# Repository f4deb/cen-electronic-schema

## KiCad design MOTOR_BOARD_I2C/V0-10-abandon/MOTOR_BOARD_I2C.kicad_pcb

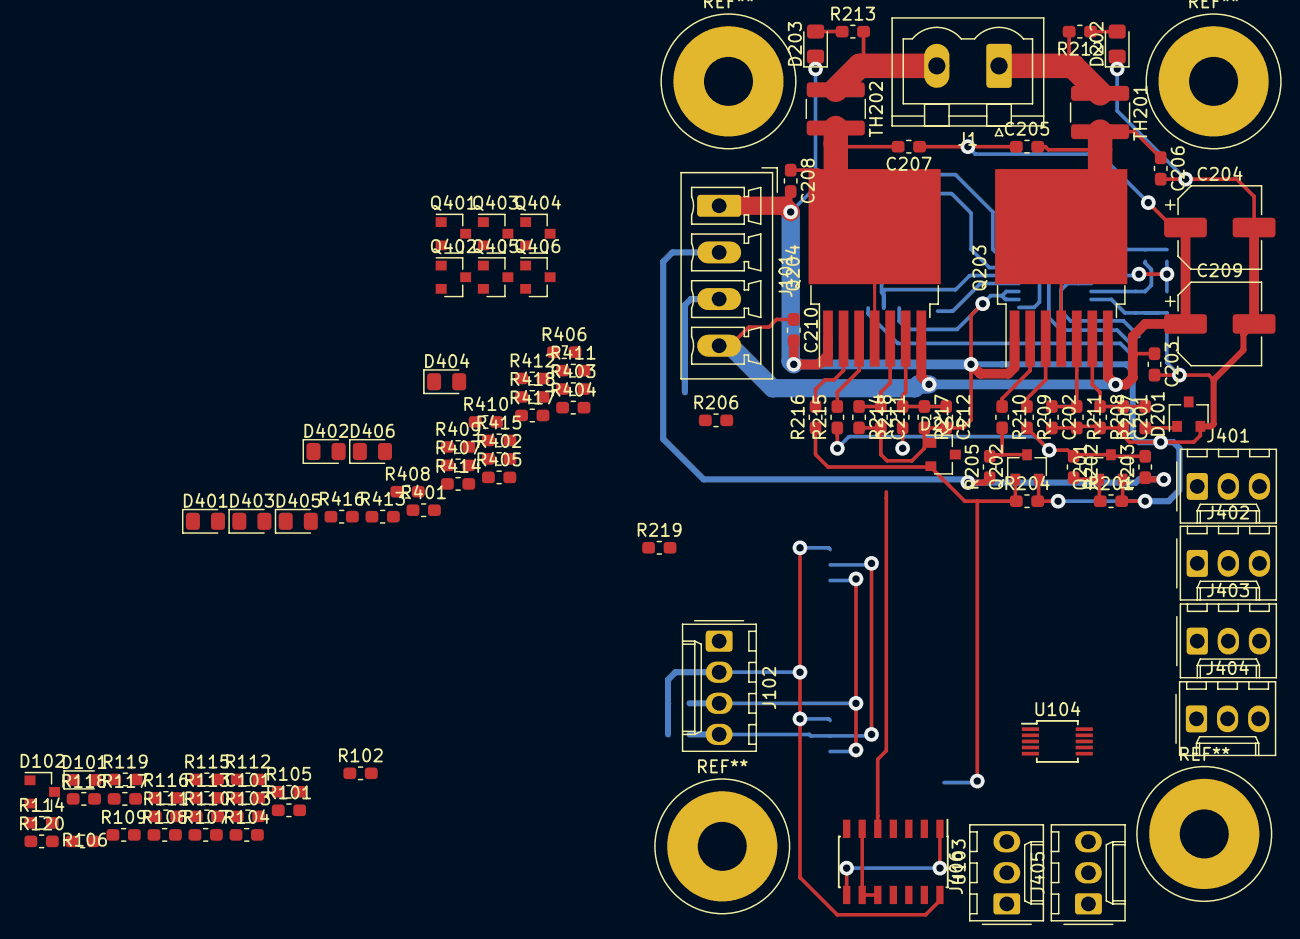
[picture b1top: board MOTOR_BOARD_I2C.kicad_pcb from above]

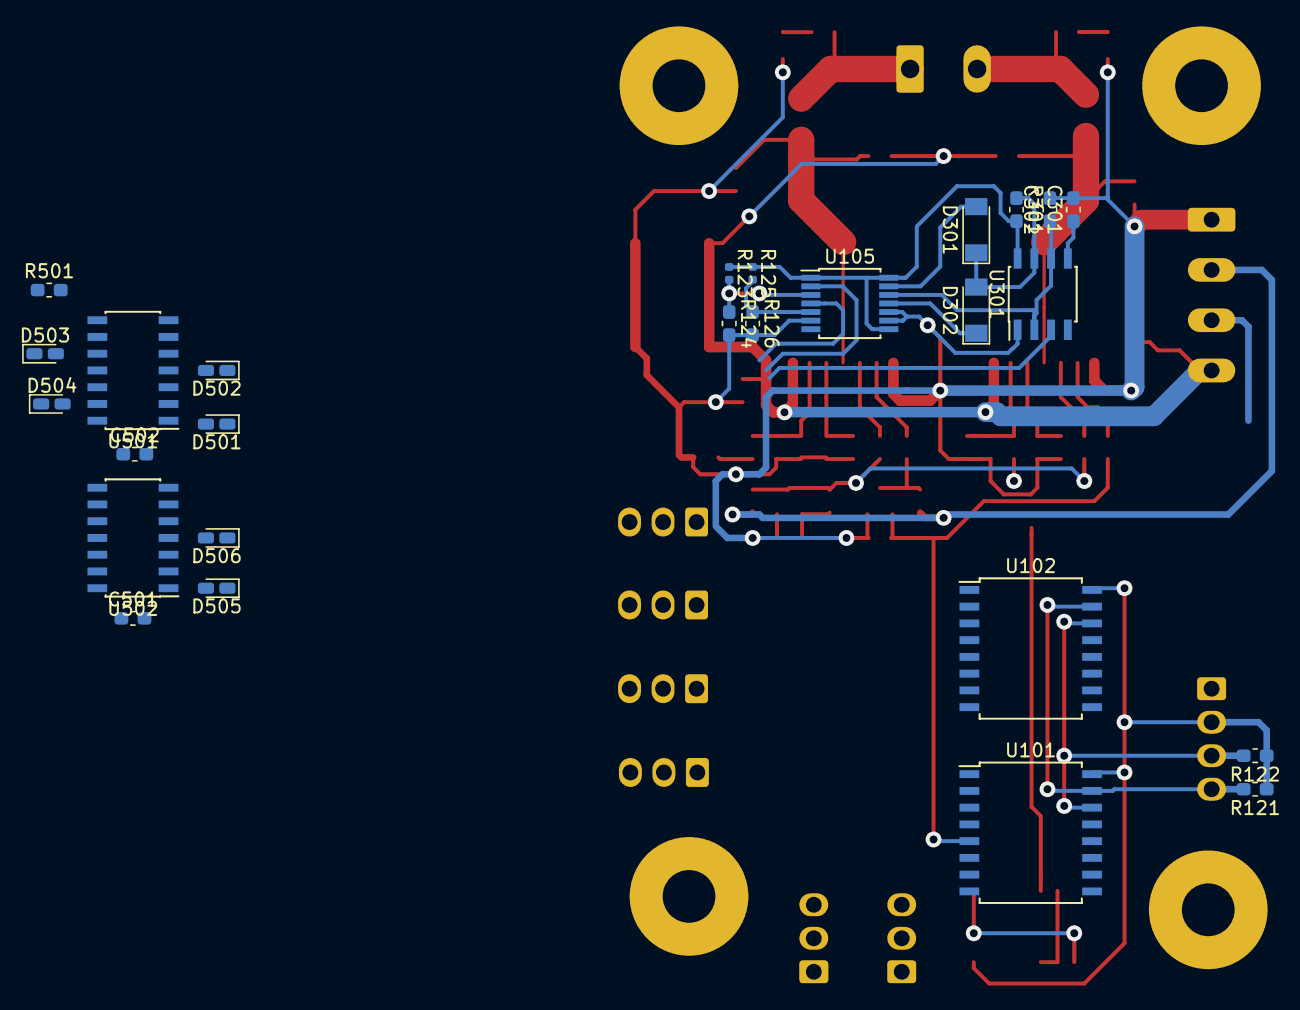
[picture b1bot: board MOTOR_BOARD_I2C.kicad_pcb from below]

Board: 2 copper layers, 131 parts (26 on the bottom side), 81 nets.

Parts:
C101, C203, C210, C501, C502: 100n; C_0603_1608Metric_Pad1.05x0.95mm_HandSolder
C201, C202, C211, C212, C302: C; C_0603_1608Metric_Pad1.05x0.95mm_HandSolder
C204, C209: 1000µ; CP_Elec_6.3x5.4
C205, C206, C207, C208: 220n; C_0603_1608Metric_Pad1.05x0.95mm_HandSolder
C301: 10n; C_0603_1608Metric_Pad1.05x0.95mm_HandSolder
D101: Jaune; LED_0603_1608Metric_Pad1.05x0.95mm_HandSolder
D102: D_Zener; SOT-23
D201, D204: D_Zener_Small_ALT; SOT-23
D202, D203, D401, D402, D403, D404, D405, D406: LED; LED_0805_2012Metric_Pad1.15x1.40mm_HandSolder
D301, D302: LL4148; D_MiniMELF
D501, D502, D503, D504, D505, D506: B140-E3; D_0603_1608Metric_Castellated
J1: Conn_01x02; PhoenixContact_MSTBVA_2,5_2-G-5,08_1x02_P5.08mm_Vertical
J101: Conn_01x04; PhoenixContact_MCV_1,5_4-G-3.81_1x04_P3.81mm_Vertical
J102: Conn_01x04; Molex_KK-254_AE-6410-04A_1x04_P2.54mm_Vertical
J401, J402, J403, J404, J405, J406: Conn_01x03_Male; Molex_KK-254_AE-6410-03A_1x03_P2.54mm_Vertical
Q201, Q202, Q401, Q402, Q403, Q404, Q405, Q406: 2N7002; SOT-23
Q203, Q204: BTN8982TA; TO-263-7_TabPin4
R101, R103, R105, R107, R109, R111, R115, R117, R119: 0; R_0603_1608Metric_Pad1.05x0.95mm_HandSolder
R102, R104, R106, R108, R110, R112, R116, R118, R120, R121, R122, R124, R126, R203, R205, R209, R210, R215, R216, R501: 10k; R_0603_1608Metric_Pad1.05x0.95mm_HandSolder
R113, R114, R405, R406, R411, R412, R417, R418: 1k; R_0603_1608Metric_Pad1.05x0.95mm_HandSolder
R123, R125: 0; R_0402_1005Metric
R201, R204, R403, R404, R409, R410, R415, R416: 100k; R_0603_1608Metric_Pad1.05x0.95mm_HandSolder
R202: NC-0; R_0603_1608Metric_Pad1.05x0.95mm_HandSolder
R206, R207, R208, R211, R212, R213, R214, R217, R218, R219, R301: R; R_0603_1608Metric_Pad1.05x0.95mm_HandSolder
R401, R402, R407, R408, R413, R414: 100; R_0603_1608Metric_Pad1.05x0.95mm_HandSolder
TH201, TH202: Thermistor; R_1218_3246Metric_Pad1.22x4.75mm_HandSolder
U101, U102: PCF8574A; SOIC-16W_7.5x10.3mm_P1.27mm
U103: 74HC00; SOIC-14_3.9x8.7mm_P1.27mm
U104: MCP3427-xUN; MSOP-10_3x3mm_P0.5mm
U105: MCP45HV31-ST; TSSOP-14_4.4x5mm_P0.65mm
U301: LM555; SOIC-8_3.9x4.9mm_P1.27mm
U501, U502: 74HC02; SOIC-14_3.9x8.7mm_P1.27mm

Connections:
+5VD: C501.1, C502.1, D401.2, D402.2, D403.2, D404.2, D405.2, D406.2, J101.2, J102.2, J401.2, J402.2, J403.2, J404.2, J405.2, J406.2, R101.1, R103.1, R105.1, R107.1, R109.1, R111.1, R114.1, R115.1, R117.1, R119.1, R121.1, R122.1, R123.1, R125.1, R203.1, R205.1, R301.2, U101.16, U102.16, U103.14, U105.1, U105.8, U105.14, U301.4, U301.8, U501.14, U502.14
+15V: C203.1, C204.1, C205.1, C207.1, C209.1, C210.1, J101.4, Q203.7, Q204.7
/IN0: Q401.3, R405.2, U102.6, U501.2
/IN1: Q403.3, R411.2, U102.7, U501.5
/IN2: Q405.3, R417.2, U102.9, U501.8
/IN3: Q402.3, R406.2, U102.10, U501.11
/IN4: Q404.3, R412.2, U102.11, U502.2
/IN5: Q406.3, R418.2, U102.12, U502.5
/IS1: R206.1, U102.4
/IS2: R219.1, U102.5
/M1A: J1.1, R212.2, TH201.1
/M1B: J1.2, R213.2, TH202.1
/PWM: U103.5, U301.3
/SCL: J102.3, R122.2, U101.14, U102.14, U105.2
/SDA: J102.4, R121.2, U101.15, U102.15, U105.4
/STOPMOTOR: U103.4, U502.13
/Sheet5DBEC701/S0: D501.2, U501.1
/Sheet5DBEC701/S1: D502.2, U501.4
/Sheet5DBEC701/S2: D503.2, U501.10
/Sheet5DBEC701/S3: D504.2, U501.13
/Sheet5DBEC701/S4: D505.2, U502.1
/Sheet5DBEC701/S5: D506.2, U502.4
/Sheet5DC0EE77/DIR1: Q202.1, R204.1, R216.1, U101.5
/Sheet5DC0EE77/PWM1: Q201.1, R201.1, R202.2, U103.3
/Sheet5DC7BBDF/Ra: D301.2, U105.13
/Sheet5DC7BBDF/Rb: D302.1, U105.11
/Sheet5DC7BBDF/Rw: C302.1, U105.12, U301.2, U301.6
GND: C101.2, C201.2, C202.2, C203.2, C204.2, C206.2, C208.2, C209.2, C210.2, C211.2, C212.2, C301.2, C302.2, C501.2, C502.2, D101.2, D102.2, D201.2, D202.1, D203.1, D204.2, J101.1, J102.1, J401.3, J402.3, J403.3, J404.3, J405.3, J406.3, Q201.2, Q202.2, Q203.1, Q204.1, Q401.2, Q402.2, Q403.2, Q404.2, Q405.2, Q406.2, R102.2, R104.2, R106.2, R108.2, R110.2, R112.2, R116.2, R118.2, R120.2, R124.2, R126.2, R201.2, R204.2, R208.2, R211.2, R214.2, R217.2, R403.2, R404.2, R409.2, R410.2, R415.2, R416.2, R501.2, U101.8, U102.8, U103.7, U105.6, U105.9, U105.10, U301.1, U501.7, U502.7
unnamed: C101.1, D102.1, R114.2
unnamed: C201.1, Q203.6, R207.2, R208.1
unnamed: C202.1, Q203.5, R211.1
unnamed: C205.2, C206.1, Q203.4, TH201.2
unnamed: C207.2, C208.1, Q204.4, TH202.2
unnamed: C211.1, Q204.5, R214.1
unnamed: C212.1, Q204.6, R217.1, R218.2
unnamed: C301.1, U301.5
unnamed: D101.1, R113.1
unnamed: D201.1, R206.2, R207.1
unnamed: D202.2, R212.1
unnamed: D203.2, R213.1
unnamed: D204.1, R218.1, R219.2
unnamed: D301.1, D302.2, R301.1, U301.7
unnamed: D401.1, R405.1
unnamed: D402.1, R406.1
unnamed: D403.1, R411.1
unnamed: D404.1, R412.1
unnamed: D405.1, R417.1
unnamed: D406.1, R418.1
unnamed: D501.1, D502.1, D503.1, D504.1, D505.1, D506.1, R501.1, U502.11, U502.12
unnamed: J401.1, R401.2
unnamed: J402.1, R402.2
unnamed: J403.1, R407.2
unnamed: J404.1, R408.2
unnamed: J405.1, R413.2
unnamed: J406.1, R414.2
unnamed: Q201.3, R202.1, R203.2, R209.2, R215.1
unnamed: Q202.3, R205.2, R210.2
unnamed: Q203.2, R210.1
unnamed: Q203.3, R209.1
unnamed: Q204.2, R216.2
unnamed: Q204.3, R215.2
unnamed: Q401.1, R401.1, R403.1
unnamed: Q402.1, R402.1, R404.1
unnamed: Q403.1, R407.1, R409.1
unnamed: Q404.1, R408.1, R410.1
unnamed: Q405.1, R413.1, R415.1
unnamed: Q406.1, R414.1, R416.1
unnamed: R101.2, R102.1, U101.1
unnamed: R103.2, R104.1, U102.1
unnamed: R105.2, R106.1, U101.2
unnamed: R107.2, R108.1, U102.2
unnamed: R109.2, R110.1, U101.3
unnamed: R111.2, R112.1, U102.3
unnamed: R115.2, R116.1
unnamed: R117.2, R118.1
unnamed: R119.2, R120.1
unnamed: R123.2, R124.1, U105.3
unnamed: R125.2, R126.1, U105.5
unnamed: U101.4, U103.2
unnamed: U103.1, U103.8
unnamed: U103.6, U103.9, U103.10

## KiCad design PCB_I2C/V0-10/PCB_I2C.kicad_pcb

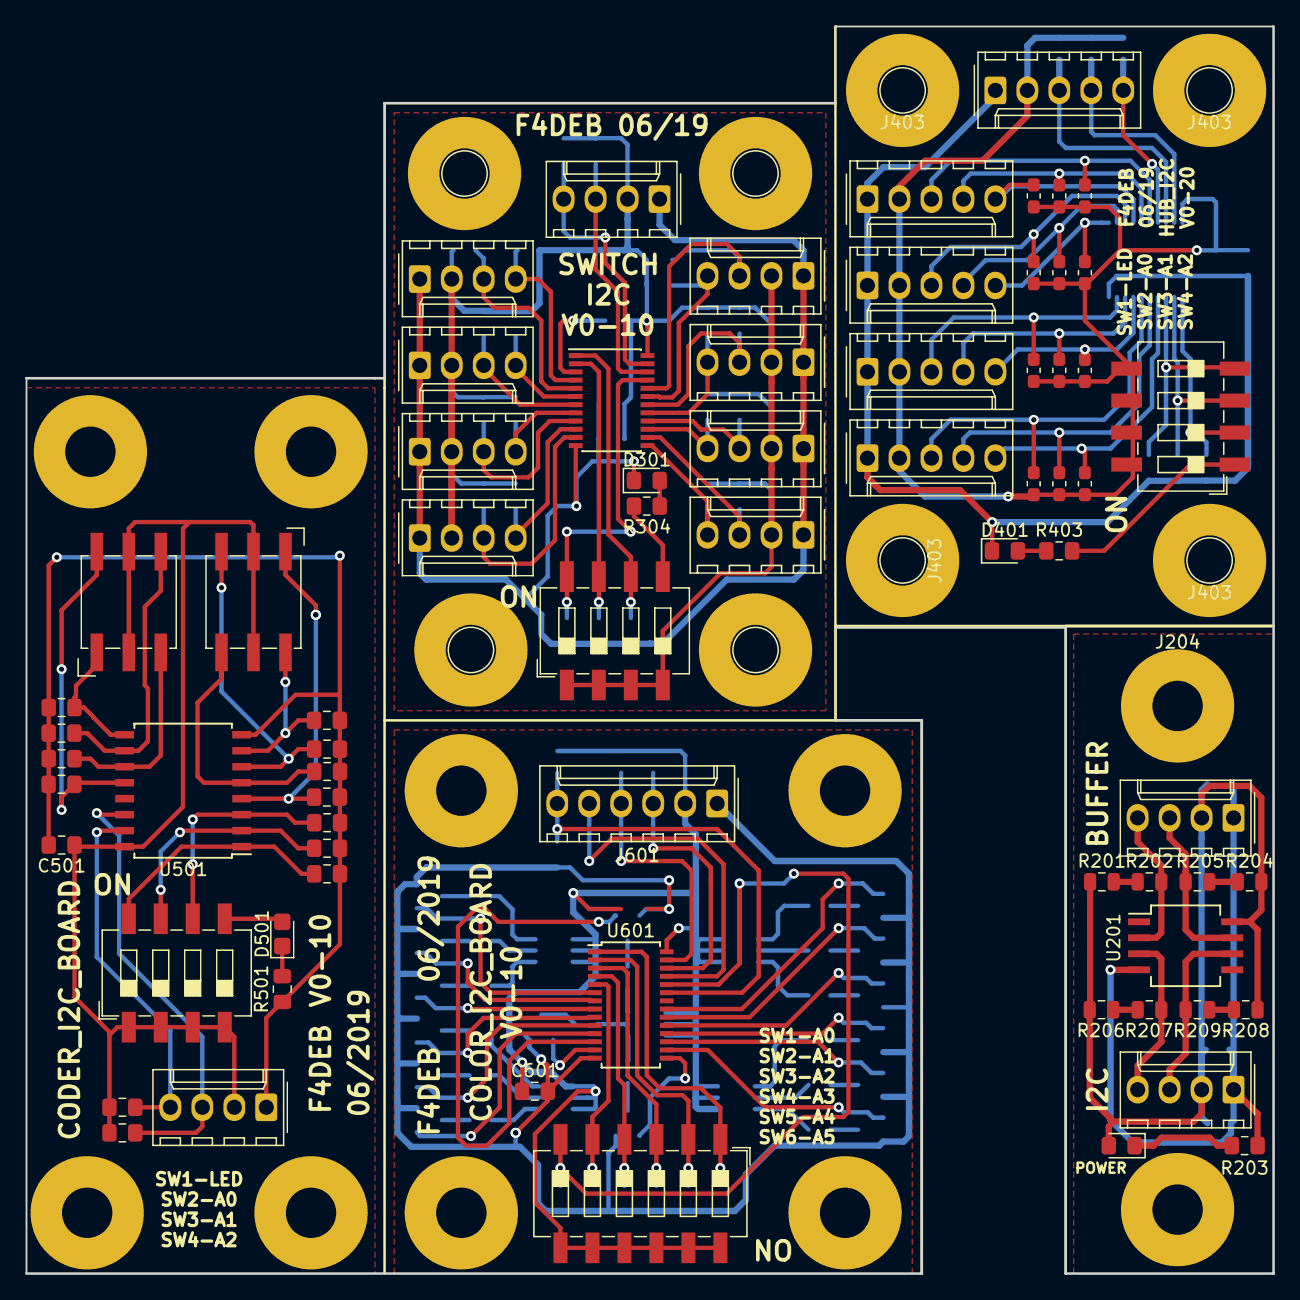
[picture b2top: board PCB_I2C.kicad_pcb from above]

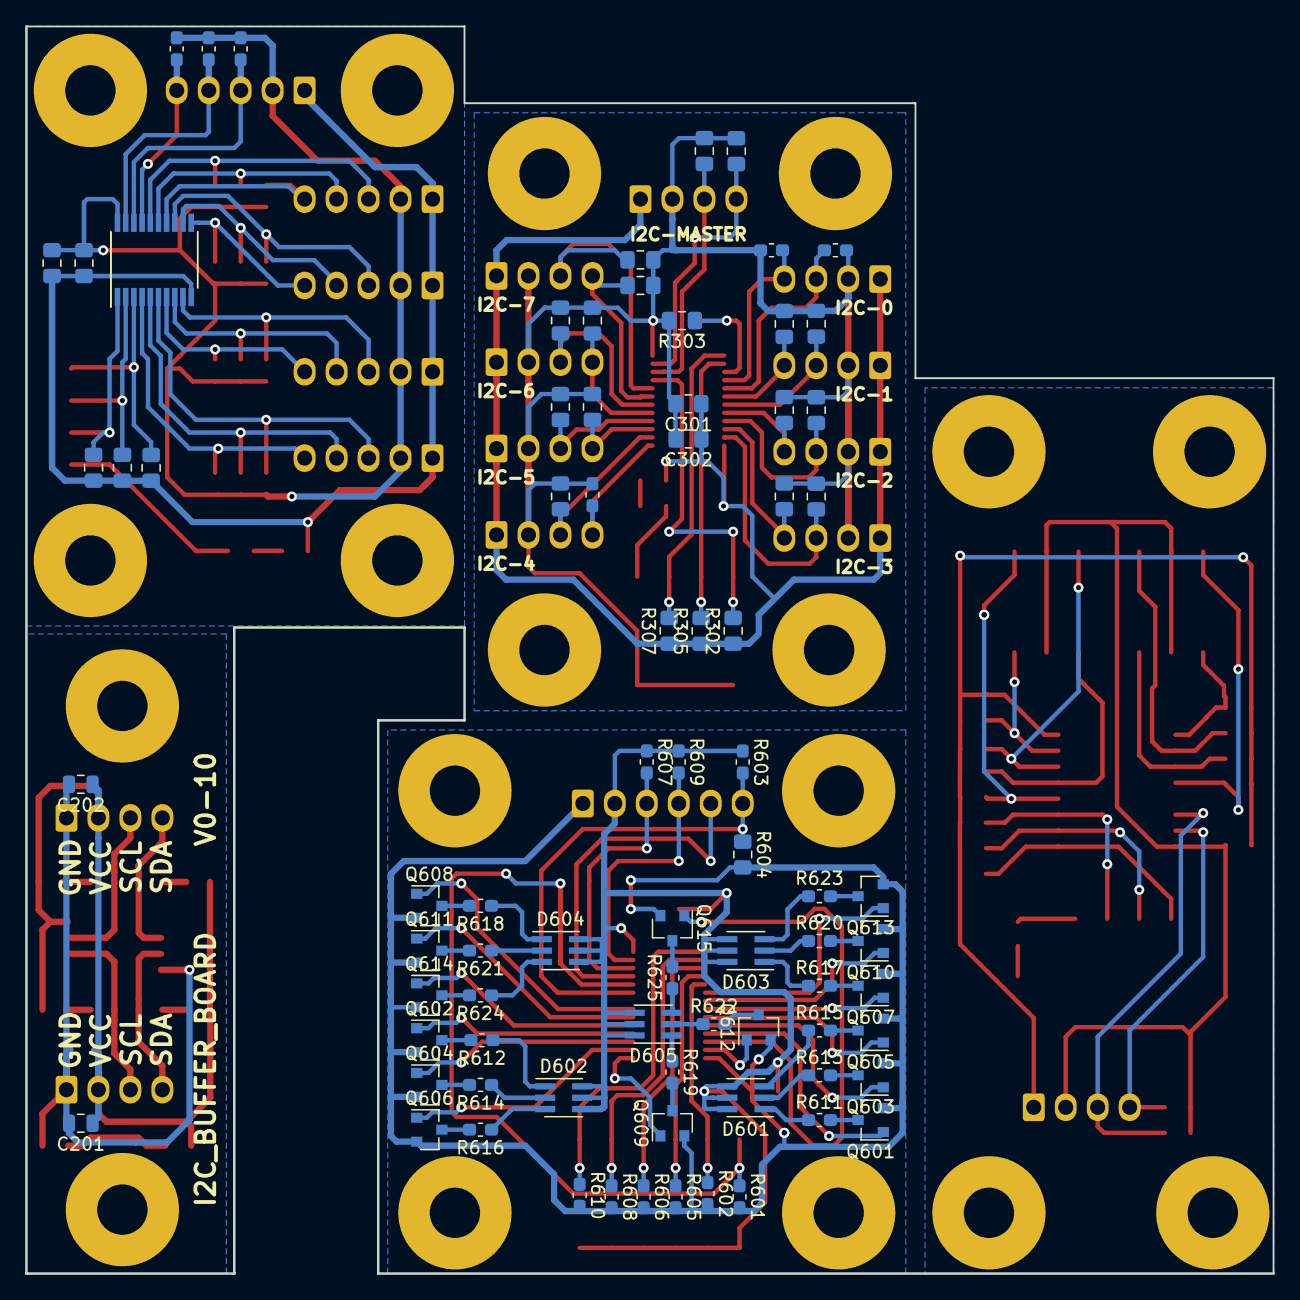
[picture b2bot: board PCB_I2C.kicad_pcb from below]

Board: 2 copper layers, 99.1 x 99.1 mm, 169 parts (80 on the bottom side), 133 nets.

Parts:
C201: 1u; C_0805_2012Metric
C202: 100n; C_0805_2012Metric
C301, C501, C601: 100n; C_0805_2012Metric_Pad1.15x1.40mm_HandSolder
C302: 1u; C_0805_2012Metric_Pad1.15x1.40mm_HandSolder
C401, C402: C; C_0805_2012Metric_Pad1.15x1.40mm_HandSolder
D201: LED Vert; LED_0805_2012Metric_Pad1.15x1.40mm_HandSolder
D301, D401: VERT; LED_0805_2012Metric_Pad1.15x1.40mm_HandSolder
D501: VERT; D_0805_2012Metric_Castellated
D601, D602, D603, D604, D605: ASMT-YTB7-0AA02; LED_Avago_PLCC6_3x2.8mm
J201, J202, J301, J302, J305, J306, J307, J308, J309, J310, J311: Conn_01x04_Male; Molex_KK-254_AE-6410-04A_1x04_P2.54mm_Vertical
J203, J204, J502, J502#2, J502#3, J502#4, J502#5, J502#6, J503, J503#2: Conn_01x01_Female; SolderWirePad_1x01_Drill2.5mm
J303, J303#2, J304, J304#2, J403, J403#2, J403#3, J403#4: Conn_01x01_Female; Pin_D1.3mm_L11.0mm_LooseFit
J401, J404, J405, J406, J407: Conn_01x05_Male; Molex_KK-254_AE-6410-05A_1x05_P2.54mm_Vertical
J501: Conn_01x04; Molex_KK-254_AE-6410-04A_1x04_P2.54mm_Vertical
J601: Conn_01x04; Molex_KK-254_AE-6410-06A_1x06_P2.54mm_Vertical
Q601, Q602, Q603, Q604, Q605, Q606, Q607, Q608, Q609, Q610, Q611, Q612, Q613, Q614, Q615: BSS138; SOT-23
R201, R204, R206, R208: 0; R_0805_2012Metric
R202, R205, R207, R209: 2k1; R_0805_2012Metric
R203, R304, R403, R501: 1k; R_0805_2012Metric_Pad1.15x1.40mm_HandSolder
R301, R306, R310, R311, R312, R313, R314, R315, R316, R318, R319, R320, R321, R322, R323: 2.1k; R_0805_2012Metric_Pad1.15x1.40mm_HandSolder
R302, R305, R307, R402, R405, R406, R502, R504, R506, R507, R508, R509, R510, R511, R512, R513, R514: 47k; R_0805_2012Metric_Pad1.15x1.40mm_HandSolder
R303, R503, R505, R604: 10k; R_0805_2012Metric_Pad1.15x1.40mm_HandSolder
R308, R309, R317: 2.1k; R_0603_1608Metric_Pad1.05x0.95mm_HandSolder
R401, R404, R407, R408, R411, R414, R417, R603, R607, R609: 10k; R_0603_1608Metric_Pad1.05x0.95mm_HandSolder
R409, R410, R412, R413, R415, R416, R418, R419: 4k7; R_0603_1608Metric_Pad1.05x0.95mm_HandSolder
R601, R602, R605, R606, R608, R610: 47k; R_0603_1608Metric_Pad1.05x0.95mm_HandSolder
R611, R612, R613, R614, R615, R616, R617, R618, R619, R620, R621, R622, R623, R624, R625: R; R_0603_1608Metric_Pad1.05x0.95mm_HandSolder
SW301, SW401, SW501: SW_DIP_x04; SW_DIP_SPSTx04_Slide_6.7x11.72mm_W8.61mm_P2.54mm_LowProfile
SW502, SW503: SW_Coded_SH-7050; Nidec_Copal_SH-7010B
SW601: SW_DIP_x06; SW_DIP_SPSTx06_Slide_6.7x16.8mm_W8.61mm_P2.54mm_LowProfile
U201: P82B715; SO-8_5.3x6.2mm_P1.27mm
U301: TCA9548APWR; TSSOP-24_4.4x7.8mm_P0.65mm
U401: TCA9544A; TSSOP-20_4.4x6.5mm_P0.65mm
U501: PCF8574A; SOIC-16W_7.5x10.3mm_P1.27mm
U601: PCA9685PW; TSSOP-28_4.4x9.7mm_P0.65mm

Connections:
/Sheet5D1060A8/B0: Q601.1, U601.11
/Sheet5D1060A8/B1: Q607.1, U601.8
/Sheet5D1060A8/B2: Q602.1, U601.18
/Sheet5D1060A8/B3: Q608.1, U601.21
/Sheet5D1060A8/B4: Q609.1, U601.15
/Sheet5D1060A8/R0: Q605.1, U601.9
/Sheet5D1060A8/R1: Q613.1, U601.6
/Sheet5D1060A8/R2: Q606.1, U601.16
/Sheet5D1060A8/R3: Q614.1, U601.19
/Sheet5D1060A8/R4: Q615.1, U601.12
/Sheet5D1060A8/V0: Q603.1, U601.10
/Sheet5D1060A8/V1: Q610.1, U601.7
/Sheet5D1060A8/V2: Q604.1, U601.17
/Sheet5D1060A8/V3: Q611.1, U601.20
/Sheet5D1060A8/V4: Q612.1, U601.13
unnamed: C201.1, C202.1, D201.2, J201.2, J202.2, R201.1, R204.1, R206.1, R208.1, U201.8
unnamed: C201.2, C202.2, J201.1, J202.1, R203.2, U201.4
unnamed: C301.1, C302.1, D301.1, J301.1, J302.1, J305.1, J306.1, J307.1, J308.1, J309.1, J310.1, J311.1, R302.1, R305.1, R307.1, U301.12
unnamed: C301.2, C302.2, J301.2, J302.2, J305.2, J306.2, J307.2, J308.2, J309.2, J310.2, J311.2, R301.1, R303.2, R306.1, R308.1, R309.1, R310.1, R311.1, R312.1, R313.1, R314.1, R315.1, R316.1, R317.1, R318.1, R319.1, R320.1, R321.1, R322.1, R323.1, SW301.1, SW301.2, SW301.3, SW301.4, U301.24
unnamed: C401.1, C402.1, D401.1, J401.1, J404.1, J405.1, J406.1, J407.1, R402.1, R405.1, R406.1, U401.10
unnamed: C401.2, C402.2, J401.2, J404.2, J405.2, J406.2, J407.2, R401.1, R404.1, R407.1, R408.1, R409.1, R410.1, R411.1, R412.1, R413.1, R414.1, R415.1, R416.1, R417.1, R418.1, R419.1, SW401.5, SW401.6, SW401.7, SW401.8, U401.20
unnamed: C501.1, J501.2, R503.1, R505.1, SW501.1, SW501.2, SW501.3, SW501.4, SW502.C, SW503.C, U501.16
unnamed: C501.2, J501.1, R501.1, R502.2, R504.2, R506.2, R507.2, R508.2, R509.2, R510.2, R511.2, R512.2, R513.2, R514.2, U501.8
unnamed: C601.1, D601.4, D601.5, D601.6, D602.4, D602.5, D602.6, D603.4, D603.5, D603.6, D604.4, D604.5, D604.6, D605.4, D605.5, D605.6, J601.2, R603.1, R607.1, R609.1, SW601.7, SW601.8, SW601.9, SW601.10, SW601.11, SW601.12, U601.28
unnamed: C601.2, J601.1, Q601.2, Q602.2, Q603.2, Q604.2, Q605.2, Q606.2, Q607.2, Q608.2, Q609.2, Q610.2, Q611.2, Q612.2, Q613.2, Q614.2, Q615.2, R601.2, R602.2, R604.2, R605.2, R606.2, R608.2, R610.2, U601.14
unnamed: D201.1, R203.1
unnamed: D301.2, R304.1
unnamed: D401.2, R403.1
unnamed: D501.1, R501.2
unnamed: D501.2, SW501.5
unnamed: D601.1, R611.1
unnamed: D601.2, R613.1
unnamed: D601.3, R615.1
unnamed: D602.1, R612.1
unnamed: D602.2, R614.1
unnamed: D602.3, R616.1
unnamed: D603.1, R617.1
unnamed: D603.2, R620.1
unnamed: D603.3, R623.1
unnamed: D604.1, R618.1
unnamed: D604.2, R621.1
unnamed: D604.3, R624.1
unnamed: D605.1, R619.1
unnamed: D605.2, R622.1
unnamed: D605.3, R625.1
unnamed: J201.3, R205.2, U201.7
unnamed: J201.4, R202.2, U201.2
unnamed: J202.3, R209.2, U201.6
unnamed: J202.4, R207.2, U201.3
unnamed: J301.3, R301.2, U301.22
unnamed: J301.4, R306.2, U301.23
unnamed: J302.3, R308.2, U301.5
unnamed: J302.4, R309.2, U301.4
unnamed: J305.3, R310.2, U301.7
unnamed: J305.4, R311.2, U301.6
unnamed: J306.3, R312.2, U301.9
unnamed: J306.4, R313.2, U301.8
unnamed: J307.3, R314.2, U301.11
unnamed: J307.4, R315.2, U301.10
unnamed: J308.3, R316.2, U301.14
unnamed: J308.4, R317.2, U301.13
unnamed: J309.3, R318.2, U301.16
unnamed: J309.4, R319.2, U301.15
unnamed: J310.3, R320.2, U301.18
unnamed: J310.4, R321.2, U301.17
unnamed: J311.3, R322.2, U301.20
unnamed: J311.4, R323.2, U301.19
unnamed: J401.3, R401.2, U401.18
unnamed: J401.4, R404.2, U401.19
unnamed: J401.5, R407.2, U401.17
unnamed: J404.3, R409.2, U401.6
unnamed: J404.4, R410.2, U401.5
unnamed: J404.5, R408.2, U401.4
unnamed: J405.3, R412.2, U401.9
unnamed: J405.4, R413.2, U401.8
unnamed: J405.5, R411.2, U401.7
unnamed: J406.3, R415.2, U401.13
unnamed: J406.4, R416.2, U401.12
unnamed: J406.5, R414.2, U401.11
unnamed: J407.3, R418.2, U401.16
unnamed: J407.4, R419.2, U401.15
unnamed: J407.5, R417.2, U401.14
unnamed: J501.3, R503.2, U501.14
unnamed: J501.4, R505.2, U501.15
unnamed: J601.3, R607.2, U601.26
unnamed: J601.4, R609.2, U601.27
unnamed: J601.5, U601.25
unnamed: J601.6, R603.2, R604.1, U601.23
unnamed: Q601.3, R611.2
unnamed: Q602.3, R612.2
unnamed: Q603.3, R613.2
unnamed: Q604.3, R614.2
unnamed: Q605.3, R615.2
unnamed: Q606.3, R616.2
unnamed: Q607.3, R617.2
unnamed: Q608.3, R618.2
unnamed: Q609.3, R619.2
unnamed: Q610.3, R620.2
unnamed: Q611.3, R621.2
unnamed: Q612.3, R622.2
unnamed: Q613.3, R623.2
unnamed: Q614.3, R624.2
unnamed: Q615.3, R625.2
unnamed: R201.2, R202.1
unnamed: R204.2, R205.1
unnamed: R206.2, R207.1
unnamed: R208.2, R209.1
unnamed: R302.2, SW301.8, U301.21
unnamed: R303.1, U301.3
unnamed: R304.2, SW301.5
unnamed: R305.2, SW301.7, U301.2
unnamed: R307.2, SW301.6, U301.1
unnamed: R402.2, SW401.4, U401.3
unnamed: R403.2, SW401.1
unnamed: R405.2, SW401.3, U401.2
unnamed: R406.2, SW401.2, U401.1
unnamed: R502.1, SW501.6, U501.3
unnamed: R504.1, SW501.7, U501.2
unnamed: R506.1, SW501.8, U501.1
unnamed: R507.1, SW502.8, U501.7
unnamed: R508.1, SW503.8, U501.12
unnamed: R509.1, SW502.4, U501.6
unnamed: R510.1, SW503.4, U501.11
unnamed: R511.1, SW502.2, U501.5
unnamed: R512.1, SW503.2, U501.10
unnamed: R513.1, SW502.1, U501.4
unnamed: R514.1, SW503.1, U501.9
unnamed: R601.1, SW601.6, U601.24
unnamed: R602.1, SW601.5, U601.5
unnamed: R605.1, SW601.4, U601.4
unnamed: R606.1, SW601.3, U601.3
unnamed: R608.1, SW601.2, U601.2
unnamed: R610.1, SW601.1, U601.1

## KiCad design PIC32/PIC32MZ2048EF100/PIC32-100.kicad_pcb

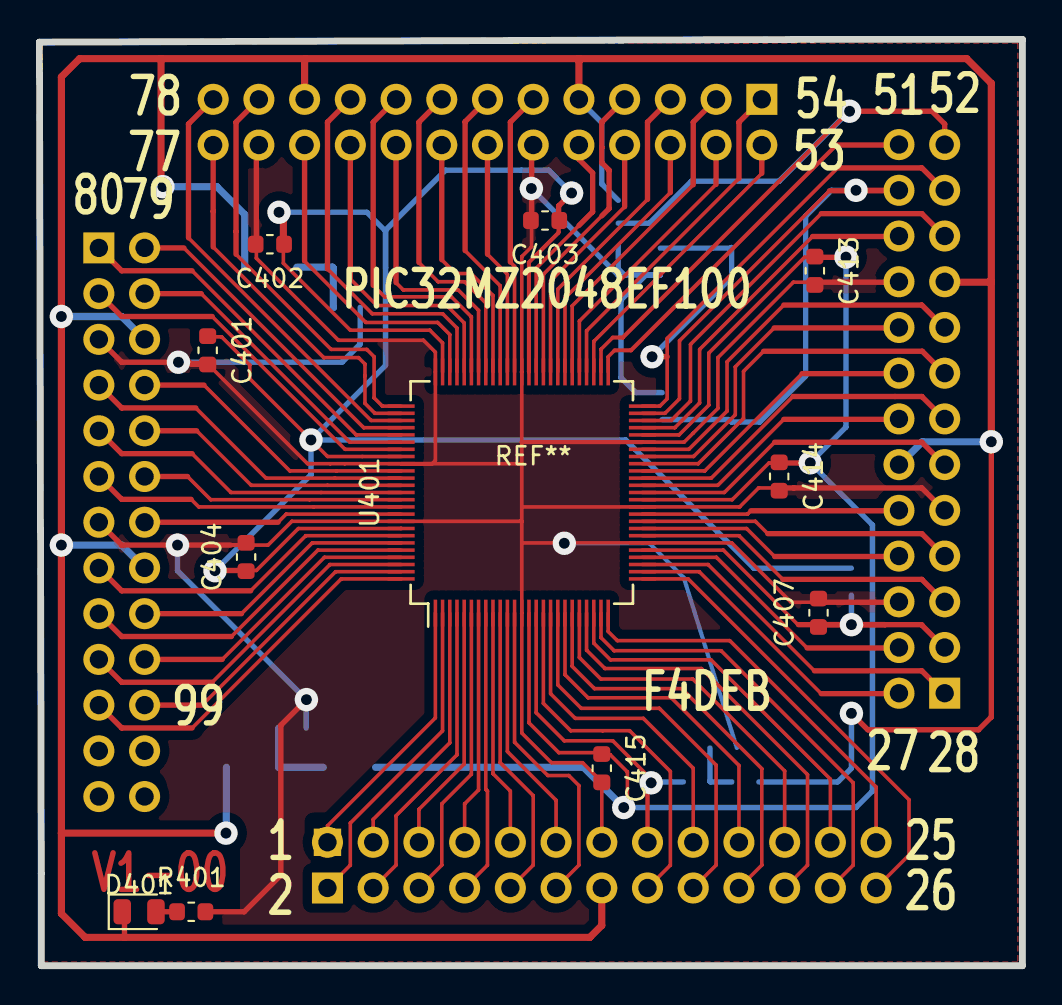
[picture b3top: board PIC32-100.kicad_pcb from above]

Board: 2 copper layers, 54.6 x 51.5 mm, 29 parts (0 on the bottom side), 93 nets.

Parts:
C401, C402, C403, C404, C407, C413, C414, C415: 100n; C_0603_1608Metric
C408, C409: 10n; C_0603_1608Metric_Pad1.05x0.95mm_HandSolder
C410: 22p; C_0603_1608Metric
C411: 100n; C_0603_1608Metric_Pad1.05x0.95mm_HandSolder
C412: 22p; C_0603_1608Metric_Pad1.05x0.95mm_HandSolder
D401: LED; LED_0805_2012Metric
L401, L402, L403, L404: Ferrite_Bead_Small; L_1206_3216Metric_Pad1.42x1.75mm_HandSolder
P401, P402, P404, P405: CONN_13X2; Socket_Strip_Straight_2x13
P403: CAVALIER2; SolderJumper-3_P2.0mm_Open_TrianglePad1.0x1.5mm
R401, R403: 1k; R_0603_1608Metric
R402: 0; R_0603_1608Metric
R404: 10k; R_0603_1608Metric_Pad1.05x0.95mm_HandSolder
U401: PIC32MZ2048EF100; TQFP-100_12x12mm_P0.4mm
X401: 24Mhz; Crystal_SMD_HC49-SD

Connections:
+3.3VA: D401.1, L401.1, L403.1, P401.13, P402.12, P402.19, P403.1, P404.9, P404.21, P405.6, P405.16, R404.2
/PIC32MZ2048EF100/1: P401.2, U401.1
/PIC32MZ2048EF100/2: P401.1, U401.2
/PIC32MZ2048EF100/3: P401.4, U401.3
/PIC32MZ2048EF100/4: P401.3, U401.4
/PIC32MZ2048EF100/5: P401.6, U401.5
/PIC32MZ2048EF100/6: P401.5, U401.6
/PIC32MZ2048EF100/7: P401.8, U401.7
/PIC32MZ2048EF100/8: P401.7, U401.8
/PIC32MZ2048EF100/9: P401.10, U401.9
/PIC32MZ2048EF100/10: P401.9, U401.10
/PIC32MZ2048EF100/11: P401.12, U401.11
/PIC32MZ2048EF100/12: P401.11, U401.12
/PIC32MZ2048EF100/15: P401.16, R403.1, U401.15
/PIC32MZ2048EF100/16: P401.15, U401.16
/PIC32MZ2048EF100/17: P401.18, U401.17
/PIC32MZ2048EF100/18: P401.17, U401.18
/PIC32MZ2048EF100/19: P401.20, U401.19
/PIC32MZ2048EF100/20: P401.19, U401.20
/PIC32MZ2048EF100/21: P401.22, U401.21
/PIC32MZ2048EF100/22: P401.21, U401.22
/PIC32MZ2048EF100/23: P401.24, U401.23
/PIC32MZ2048EF100/24: P401.23, U401.24
/PIC32MZ2048EF100/25: P401.26, U401.25
/PIC32MZ2048EF100/26: P401.25, U401.26
/PIC32MZ2048EF100/27: P402.2, U401.27
/PIC32MZ2048EF100/28: P402.1, U401.28
/PIC32MZ2048EF100/29: P402.4, U401.29
/PIC32MZ2048EF100/30: C407.1, P402.3, R402.2, U401.30
/PIC32MZ2048EF100/32: P402.5, U401.32
/PIC32MZ2048EF100/33: P402.8, U401.33
/PIC32MZ2048EF100/34: P402.7, U401.34
/PIC32MZ2048EF100/35: P402.10, U401.35
/PIC32MZ2048EF100/38: P402.11, U401.38
/PIC32MZ2048EF100/39: P402.14, U401.39
/PIC32MZ2048EF100/40: P402.13, U401.40
/PIC32MZ2048EF100/41: P402.16, U401.41
/PIC32MZ2048EF100/42: P402.15, U401.42
/PIC32MZ2048EF100/43: P402.18, U401.43
/PIC32MZ2048EF100/44: P402.17, U401.44
/PIC32MZ2048EF100/47: P402.22, U401.47
/PIC32MZ2048EF100/48: P402.21, U401.48
/PIC32MZ2048EF100/49: C410.1, P402.24, U401.49, X401.2
/PIC32MZ2048EF100/50: C412.1, P402.23, U401.50, X401.1
/PIC32MZ2048EF100/51: P402.26, U401.51
/PIC32MZ2048EF100/52: P402.25, P403.2, U401.52
/PIC32MZ2048EF100/53: P404.2, U401.53
/PIC32MZ2048EF100/54: P404.1, U401.54
/PIC32MZ2048EF100/55: P404.4, U401.55
/PIC32MZ2048EF100/56: P404.3, U401.56
/PIC32MZ2048EF100/57: P404.6, U401.57
/PIC32MZ2048EF100/58: P404.5, U401.58
/PIC32MZ2048EF100/59: P404.8, U401.59
/PIC32MZ2048EF100/60: P404.7, U401.60
/PIC32MZ2048EF100/61: P404.10, U401.61
/PIC32MZ2048EF100/64: P404.11, U401.64
/PIC32MZ2048EF100/65: P404.14, U401.65
/PIC32MZ2048EF100/66: P404.13, U401.66
/PIC32MZ2048EF100/67: P404.16, U401.67
/PIC32MZ2048EF100/68: P404.15, U401.68
/PIC32MZ2048EF100/69: P404.18, U401.69
/PIC32MZ2048EF100/70: P404.17, U401.70
/PIC32MZ2048EF100/71: P404.20, U401.71
/PIC32MZ2048EF100/72: P404.19, U401.72
/PIC32MZ2048EF100/73: P404.22, U401.73
/PIC32MZ2048EF100/76: P404.23, U401.76
/PIC32MZ2048EF100/77: P404.26, U401.77
/PIC32MZ2048EF100/78: P404.25, U401.78
/PIC32MZ2048EF100/79: P405.2, U401.79
/PIC32MZ2048EF100/80: P405.1, U401.80
/PIC32MZ2048EF100/81: P405.4, U401.81
/PIC32MZ2048EF100/82: P405.3, U401.82
/PIC32MZ2048EF100/85: P405.8, U401.85
/PIC32MZ2048EF100/86: P405.7, U401.86
/PIC32MZ2048EF100/87: P405.10, U401.87
/PIC32MZ2048EF100/88: P405.9, U401.88
/PIC32MZ2048EF100/89: P405.12, U401.89
/PIC32MZ2048EF100/90: P405.11, U401.90
/PIC32MZ2048EF100/91: P405.14, U401.91
/PIC32MZ2048EF100/94: P405.15, U401.94
/PIC32MZ2048EF100/95: P405.18, U401.95
/PIC32MZ2048EF100/96: P405.17, U401.96
/PIC32MZ2048EF100/97: P405.20, U401.97
/PIC32MZ2048EF100/98: P405.19, U401.98
/PIC32MZ2048EF100/99: P405.22, U401.99
/PIC32MZ2048EF100/100: P405.21, U401.100
GNDA: C401.2, C402.2, C403.2, C404.2, C407.2, C408.2, C409.2, C410.2, C411.2, C412.2, C413.2, C414.2, C415.2, P401.14, P402.6, P402.9, P402.20, P403.3, P404.12, P404.24, P405.5, P405.13, R401.2, U401.13, U401.31, U401.36, U401.45, U401.63, U401.75, U401.84, U401.92
unnamed: C401.1, C402.1, C403.1, C404.1, L402.2, R402.1, U401.62, U401.74, U401.83, U401.93
unnamed: C408.1, L401.2, L402.1
unnamed: C409.1, L403.2, L404.1
unnamed: C411.1, R403.2, R404.1
unnamed: C413.1, C414.1, C415.1, L404.2, U401.14, U401.37, U401.46
unnamed: D401.2, R401.1

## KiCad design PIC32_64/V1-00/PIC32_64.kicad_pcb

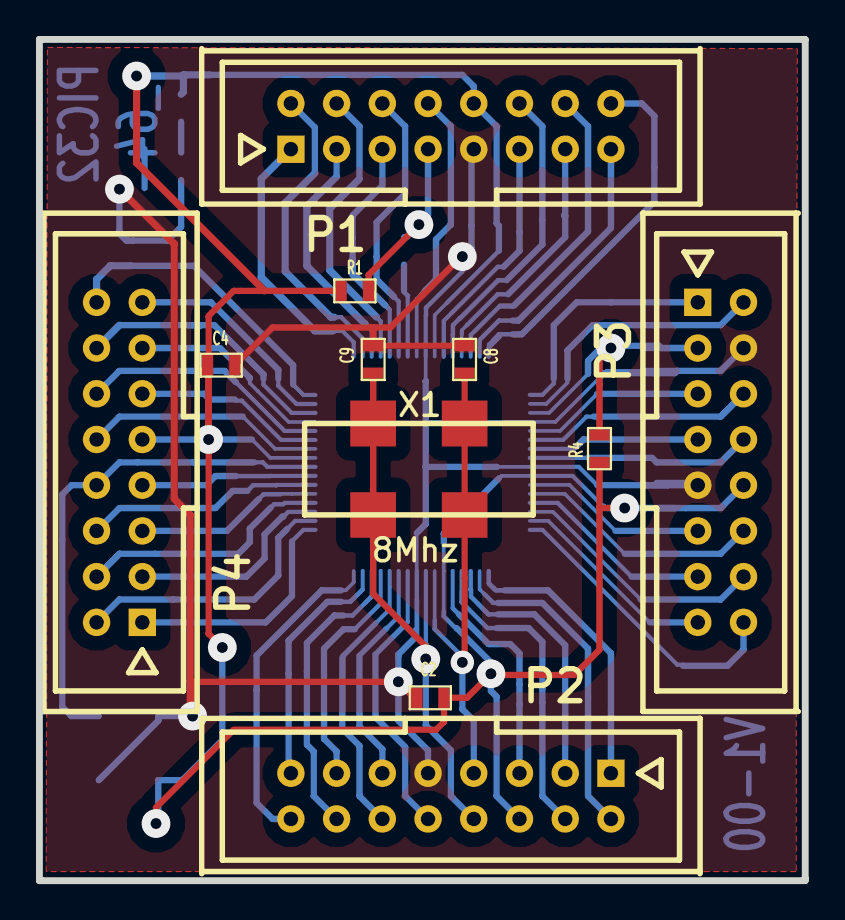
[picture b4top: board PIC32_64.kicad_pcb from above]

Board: 2 copper layers, 42.5 x 46.7 mm, 20 parts (0 on the bottom side), 60 nets.

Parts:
C1, C2, C3, C4, C5, C8, C9: 100n; SM0603_Capa
C6, C7: 10u/10V; SM1206POL
D1: LED; SM0603
P1, P2, P3, P4: CONN_8X2; he10-16d
R1: 10k; SM0603_Resistor
R2: 470; SM0603_Resistor
R3: 1k; SM0603_Resistor
R4: 10; SM0603_Resistor
U1: PIC32MX795F512H; TQFP_64
X1: 8Mhz; QTZ

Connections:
+3.3V: C1.1, C2.1, C3.1, C4.1, C6.1, D1.1, P1.10, P2.6, P3.10, P4.9, R1.2, R4.1, U1.10, U1.26, U1.38, U1.57
/1: P1.1, U1.1
/2: P1.2, U1.2
/3: P1.3, U1.3
/4: P1.4, U1.4
/5: P1.5, U1.5
/6: P1.6, U1.6
/7: P1.7, R1.1, R2.2
/8: P1.8, U1.8
/11: P1.11, U1.11
/12: P1.12, U1.12
/13: P1.13, U1.13
/14: P1.14, U1.14
/15: P1.15, U1.15
/16: P1.16, U1.16
/17: P3.1, U1.17
/18: P3.2, U1.18
/19: C5.1, P3.3, R4.2, U1.19
/21: P3.5, U1.21
/22: P3.6, U1.22
/23: P3.7, U1.23
/24: P3.8, U1.24
/27: P3.11, U1.27
/28: P3.12, U1.28
/29: P3.13, U1.29
/30: P3.14, U1.30
/31: P3.15, U1.31
/32: P3.16, U1.32
/33: P2.1, U1.33
/34: P2.2, U1.34
/35: P2.3, U1.35
/36: P2.4, U1.36
/37: P2.5, U1.37
/39: C8.1, P2.7, U1.39, X1.2
/40: C9.1, P2.8, U1.40, X1.1
/42: P2.10, U1.42
/43: P2.11, U1.43
/44: P2.12, U1.44
/45: P2.13, U1.45
/46: P2.14, U1.46
/47: P2.15, U1.47
/48: P2.16, U1.48
/49: P4.1, U1.49
/50: P4.2, U1.50
/51: P4.3, U1.51
/52: P4.4, U1.52
/53: P4.5, U1.53
/54: P4.6, U1.54
/55: P4.7, U1.55
/56: C7.1, P4.8, U1.56
/58: P4.10, U1.58
/59: P4.11, U1.59
/60: P4.12, U1.60
/61: P4.13, U1.61
/62: P4.14, U1.62
/63: P4.15, U1.63
/64: P4.16, U1.64
GND: C1.2, C2.2, C3.2, C4.2, C5.2, C6.2, C7.2, C8.2, C9.2, P1.9, P2.9, P3.4, P3.9, R3.2, U1.9, U1.20, U1.25, U1.41
unnamed: R2.1, U1.7
unnamed: D1.2, R3.1
